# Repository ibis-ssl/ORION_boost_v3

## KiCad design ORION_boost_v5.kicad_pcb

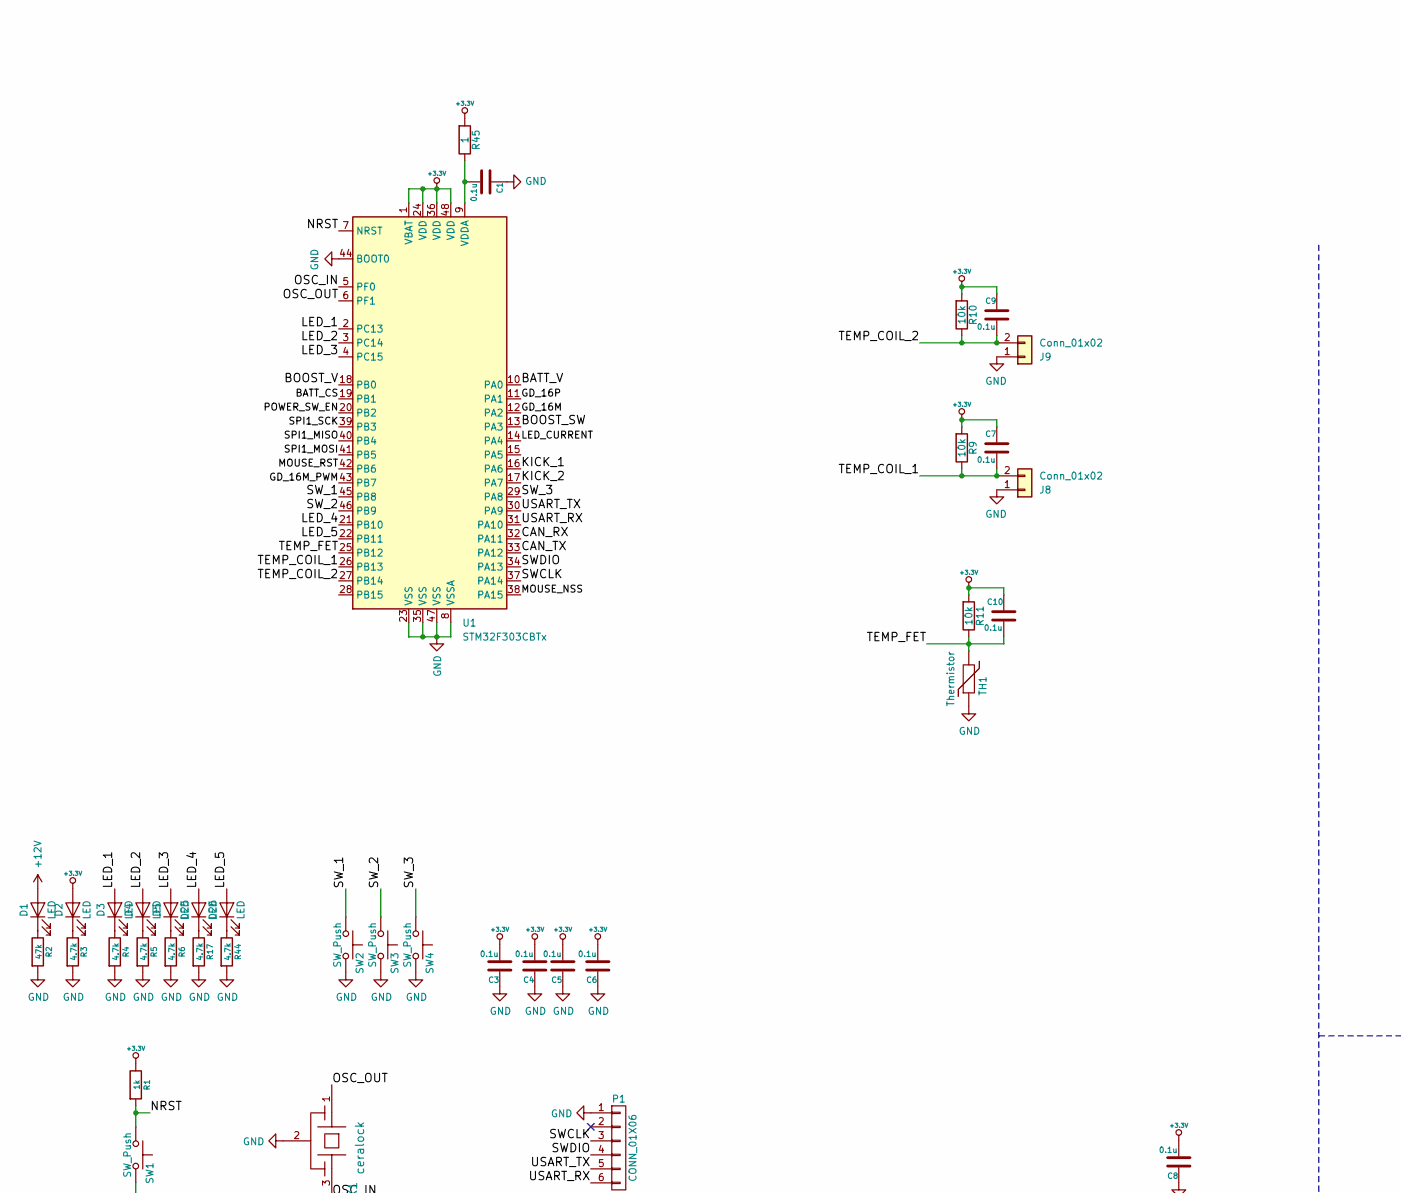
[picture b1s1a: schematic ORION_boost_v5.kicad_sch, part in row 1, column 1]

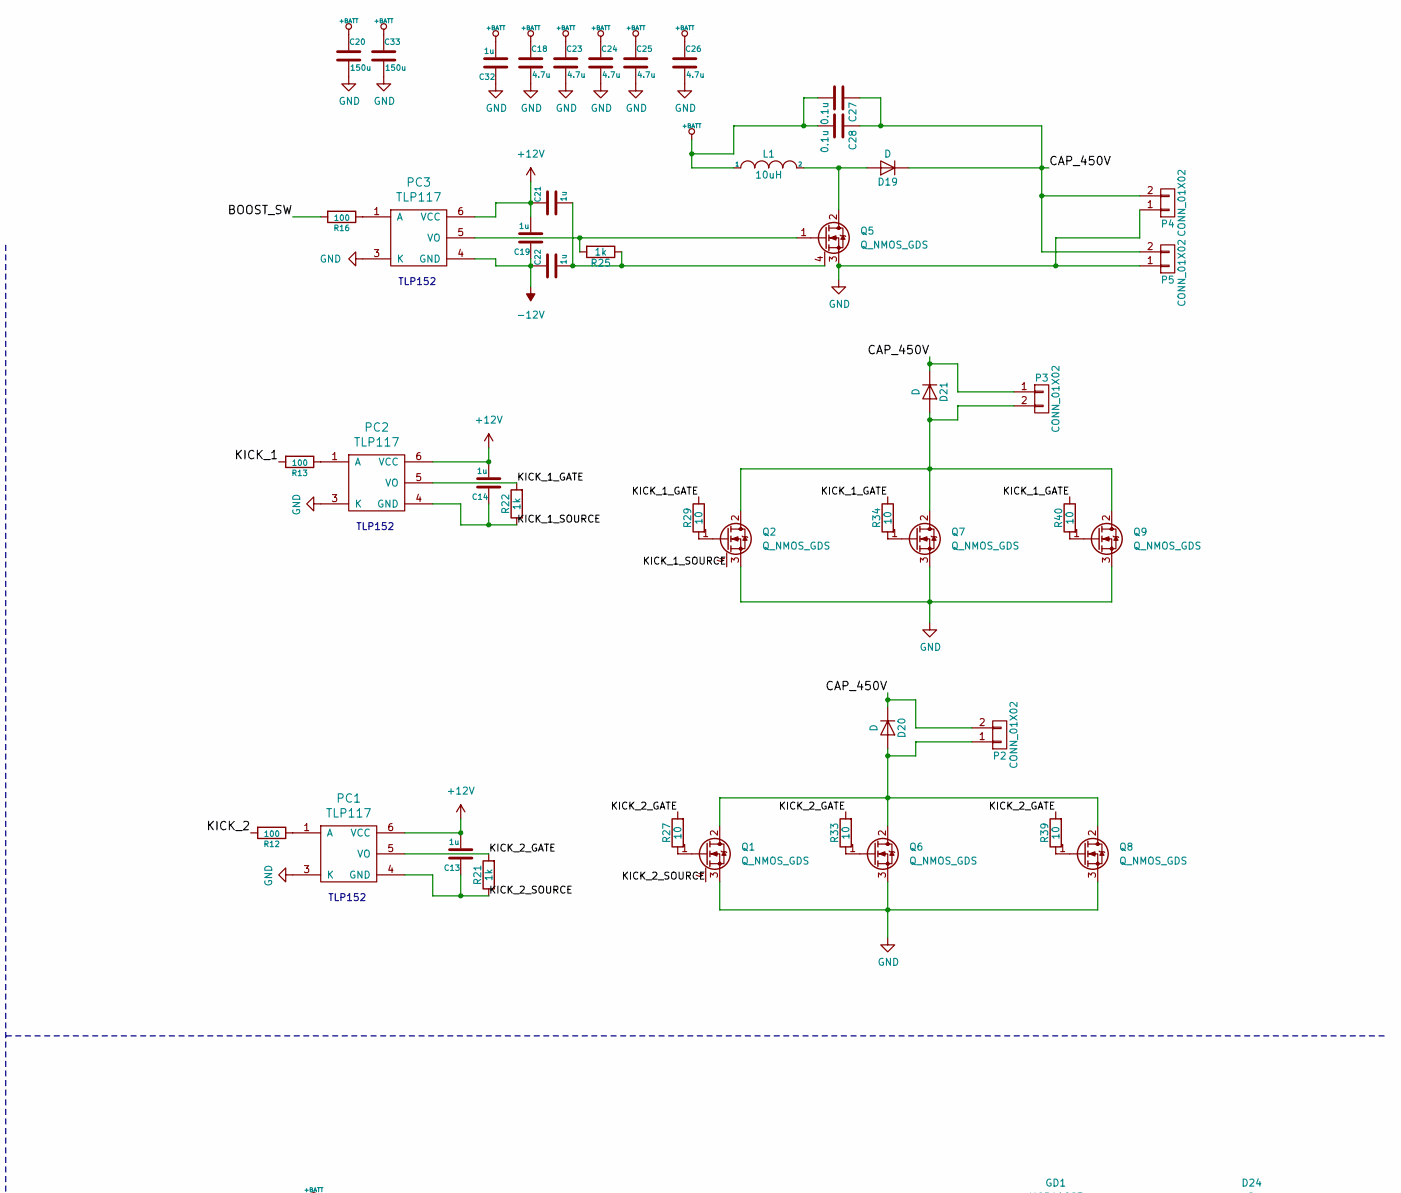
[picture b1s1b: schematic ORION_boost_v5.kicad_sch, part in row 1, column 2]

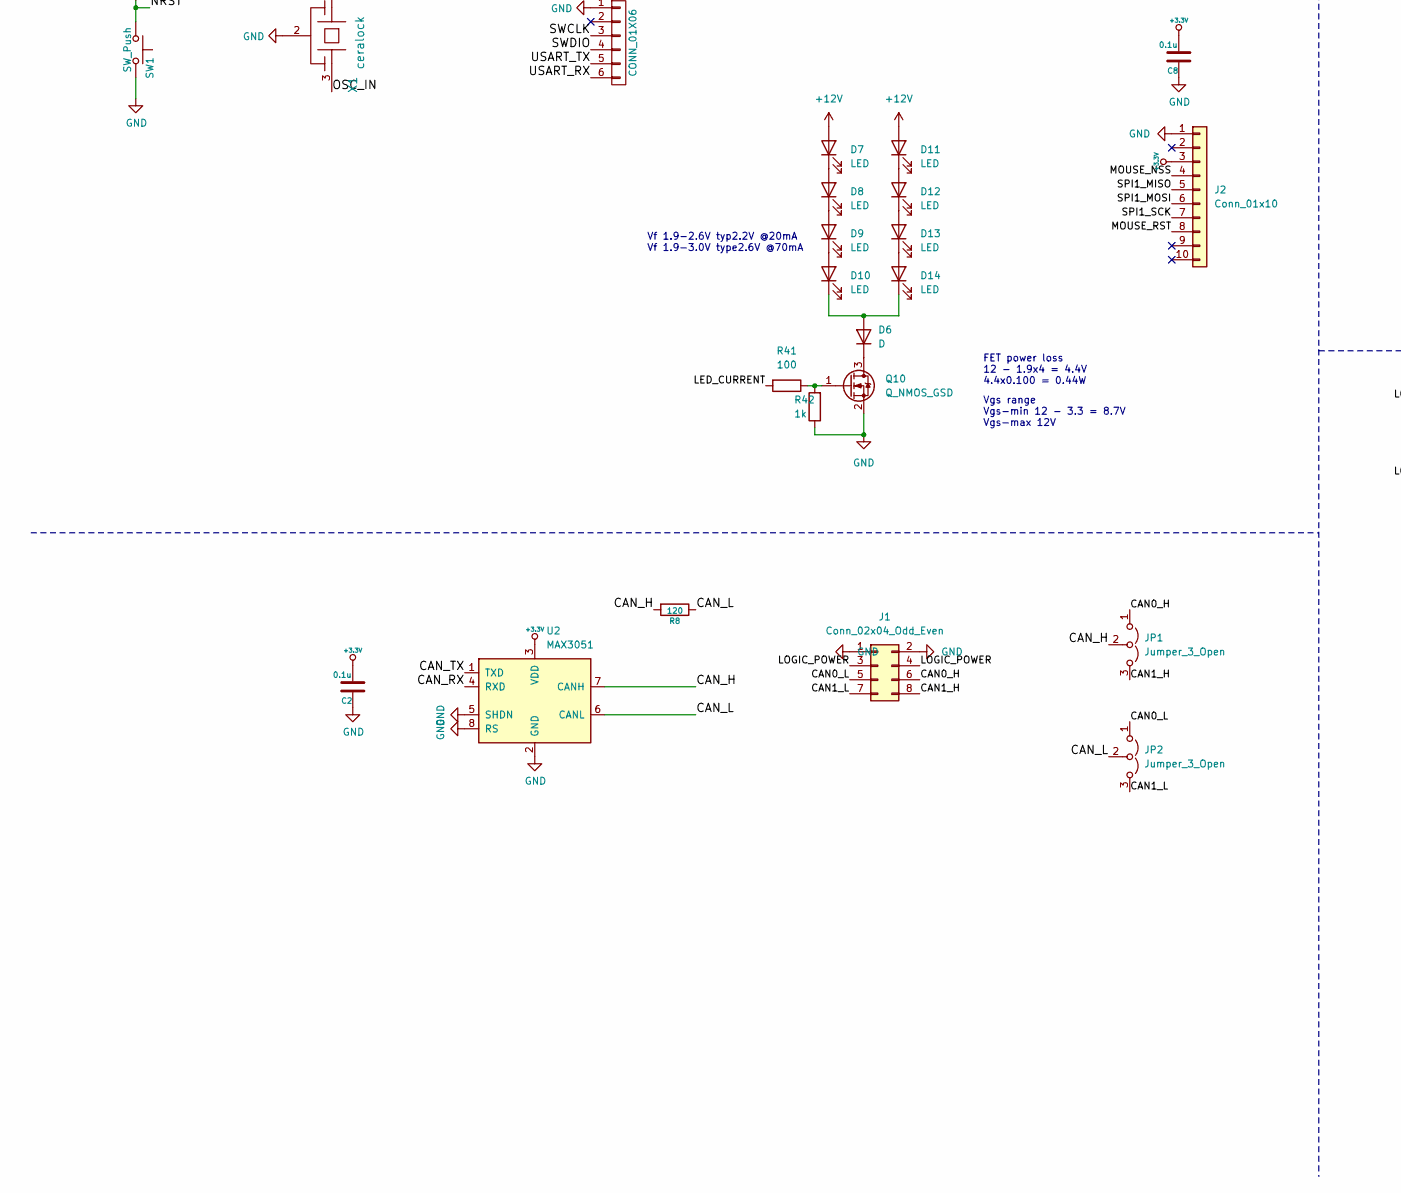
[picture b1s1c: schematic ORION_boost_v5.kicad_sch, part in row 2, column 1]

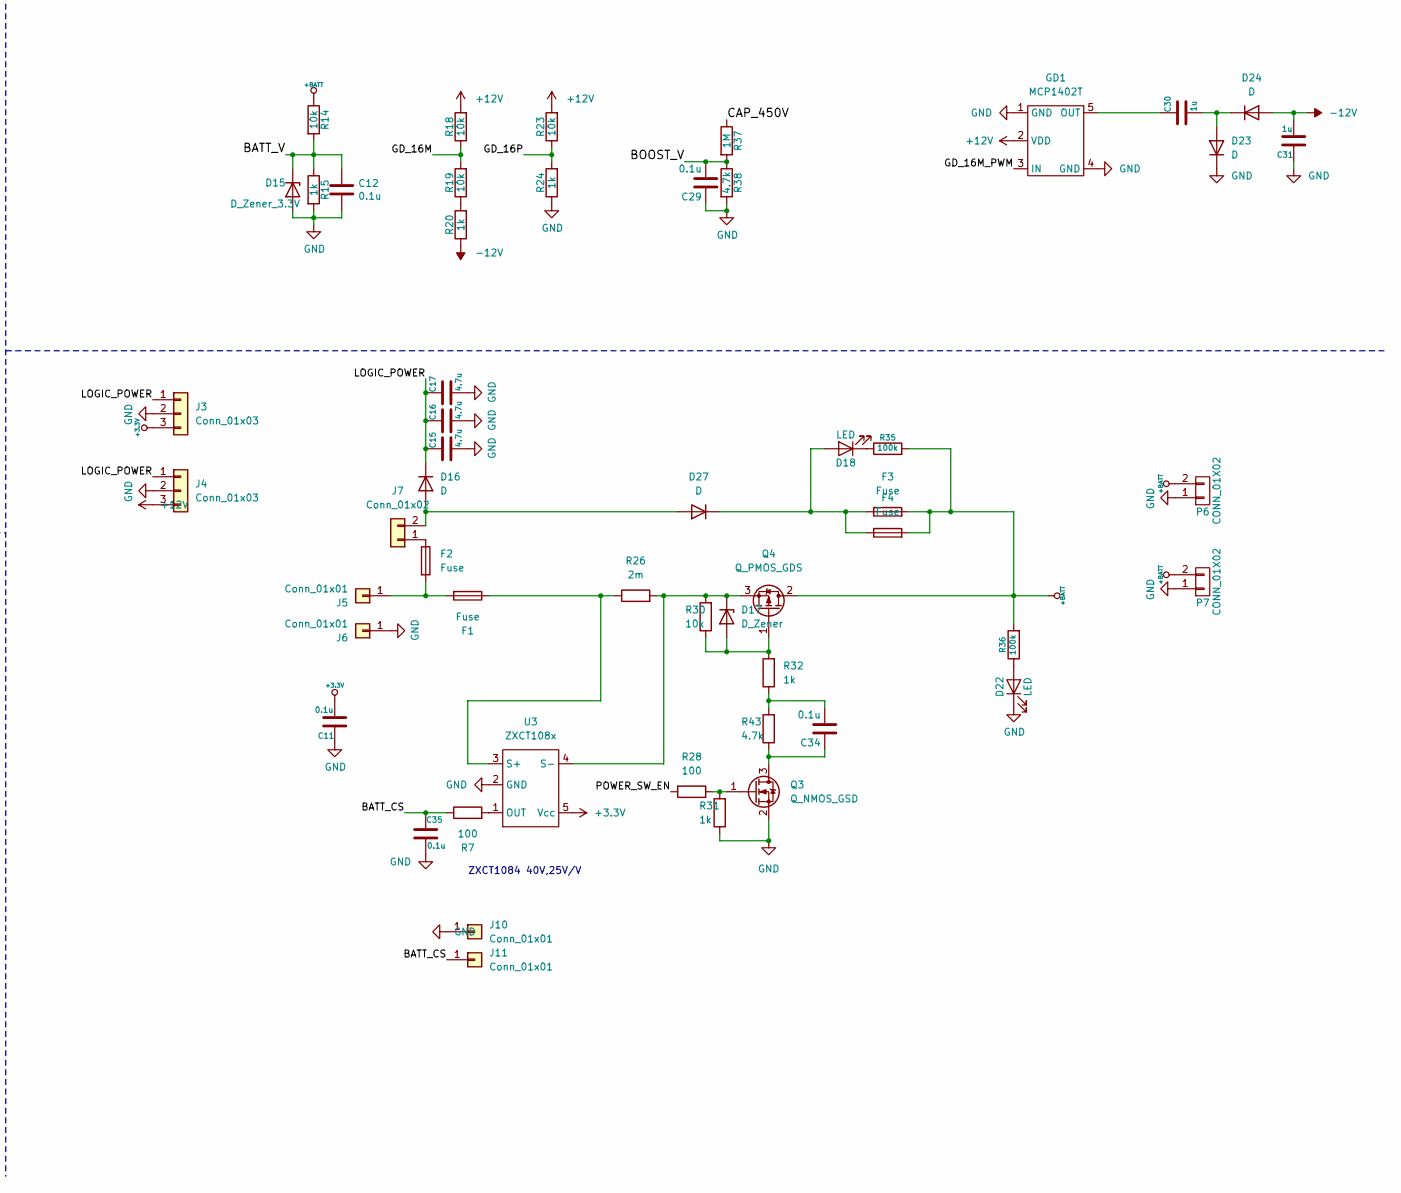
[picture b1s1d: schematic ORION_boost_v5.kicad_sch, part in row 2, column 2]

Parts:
C1, C2, C3, C4, C5, C6, C7, C8, C9, C10, C11, C12, C29, C34, C35: 0.1u; C_0603_1608Metric
C13, C14, C19, C21, C22, C30, C31, C32: 1u; C_0603_1608Metric
C15, C16, C17, C18, C23, C24, C25, C26: 4.7u; C_1206_3216Metric
C20, C33: 150u; CP_Radial_D8.0mm_P3.50mm
C27, C28: 0.1u; C_Rect_L16.5mm_W5.0mm_P15.00mm_MKT
D1, D2, D3, D4, D5, D18, D22, D25, D26: LED; LED_0603_1608Metric
D6: D; D_PowerDI-123
D7, D8, D9, D10, D11, D12, D13, D14: LED; LED_D3.0mm
D15: D_Zener_3.3V; D_SOD-323_HandSoldering
D16, D27: D; D_SMA
D17: D_Zener; D_SOD-323_HandSoldering
D19, D20, D21: D; TO-252-2-RD
D23, D24: D; D_SOD-323_HandSoldering
F1: Fuse; Reusable_Breaker_Top
F2: Fuse; C_Disc_D8.0mm_W2.5mm_P5.00mm
F3, F4: Fuse; Fuse_1210_3225Metric
GD1: MCP1402T; SOT-23-5
J1: Conn_02x04_Odd_Even; Hirose_DF11-8DP-2DSA_2x04_P2.00mm_Vertical
J2: Conn_01x10; PinSocket_1x10_P2.54mm_Vertical
J3, J4: Conn_01x03; VX07805-500
J5, J6: Conn_01x01; TestPoint_Plated_Hole_D3.0mm
J7: Conn_01x02; JST_PH_B2B-PH-K_1x02_P2.00mm_Vertical
J8, J9: Conn_01x02; PinHeader_2x01_P2.00mm_Vertical_SMD
J10, J11: Conn_01x01; WireSoldingPad
JP1, JP2: Jumper_3_Open; SolderJumper-3_P1.3mm_Open_RoundedPad1.0x1.5mm
L1: 10uH; L_Bourns_SRP1770TA_16.9x16.9mm
P1: CONN_01X06; ZH_B6B-ZR
P2, P3, P4, P5: CONN_01X02; Hirose_DF63M-2P-3.96DSA_1x02_P3.96mm_Vertical_pinless
P6, P7: CONN_01X02; AMASS_XT30U-M_1x02_P5.0mm_Vertical
PC1, PC2, PC3: TLP117; SSO-6_6.8x4.6mm_P1.27mm_Clearance8mm
Q1, Q2: Q_NMOS_GDS; TO-252-2_diff
Q3, Q10: Q_NMOS_GSD; SOT-23
Q4: Q_PMOS_GDS; TO-252-2
Q5: Q_NMOS_GDS; TO-220F-3_Horizontal_TabDown_HV_INV_diff
Q6, Q7, Q8, Q9: Q_NMOS_GDS; TO-252-2
R1, R15, R20, R21, R22, R24, R25, R31, R32, R42: 1k; R_0603_1608Metric
R2: 47k; R_0603_1608Metric
R3, R4, R5, R6, R17, R38, R43, R44: 4.7k; R_0603_1608Metric
R7, R12, R13, R16, R28, R41: 100; R_0603_1608Metric
R8: 120; R_0603_1608Metric
R9, R10, R11, R14, R18, R19, R23, R30: 10k; R_0603_1608Metric
R26: 2m; R_1020_2550Metric
R27, R29, R33, R34, R39, R40: 10; R_0603_1608Metric
R35, R36: 100k; R_0603_1608Metric
R37: 1M; R_1206_3216Metric
R45: 1; R_0603_1608Metric
SW1, SW2, SW3, SW4: SW_Push; SW_Push_SPST_NO_Alps_SKRK
TH1: Thermistor; R_0603_1608Metric
U1: STM32F303CBTx; LQFP-48_7x7mm_P0.5mm
U2: MAX3051; SO-8_3.9x4.9mm_P1.27mm
U3: ZXCT108x; SOT-23-5
X1: ceralock; Resonator_SMD_Murata_CSTxExxV-3Pin_3.0x1.1mm

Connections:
+3.3V: C2.2, C3.2, C4.2, C5.2, C6.2, C7.1, C8.2, C9.1, C10.1, C11.2, D2.2 (A), J2.3, J3.3, R1.1, R9.2, R10.2, R11.2, R45.2, U1.1 (VBAT), U1.24 (VDD), U1.36 (VDD), U1.48 (VDD), U2.3 (VDD), U3.5 (Vcc)
+12V: C13.2, C14.2, C19.2, C21.1, D1.2 (A), D7.2 (A), D11.2 (A), GD1.2 (VDD), J4.3, PC1.6 (VCC), PC2.6 (VCC), PC3.6 (VCC), R18.2, R23.2
+BATT: C18.1, C20.1, C23.1, C24.1, C25.1, C26.1, C27.2, C28.2, C32.2, C33.1, F3.2, F4.2, L1.1, P6.2, P7.2, Q4.2 (D), R14.1, R35.2, R36.2
-12V: C19.1, C22.1, C31.2, D24.2 (A), PC3.4 (GND), R20.1
/BATT_CS: C35.1, J11.1, R7.1, U1.19 (PB1)
/BATT_V: C12.2, D15.1 (K), R14.2, R15.1, U1.10 (PA0)
/BOOST_SW: R16.2, U1.13 (PA3)
/BOOST_V: C29.2, R37.2, R38.1, U1.18 (PB0)
/CAN0_H: J1.6, JP1.1 (A)
/CAN0_L: J1.5, JP2.1 (A)
/CAN1_H: J1.8, JP1.3 (B)
/CAN1_L: J1.7, JP2.3 (B)
/CAN_H: JP1.2 (C), R8.2, U2.7 (CANH)
/CAN_L: JP2.2 (C), R8.1, U2.6 (CANL)
/CAN_RX: U1.32 (PA11), U2.4 (RXD)
/CAN_TX: U1.33 (PA12), U2.1 (TXD)
/CAP_450V: C27.1, C28.1, D19.1 (K), D20.1 (K), D21.1 (K), P2.2, P3.1, P4.2, P5.2, R37.1
/GD_16M: R18.1, R19.2, U1.12 (PA2)
/GD_16M_PWM: GD1.3 (IN), U1.43 (PB7)
/GD_16P: R23.1, R24.2, U1.11 (PA1)
/KICK_1: R13.2, U1.16 (PA6)
/KICK_1_GATE: PC2.5 (VO), R22.2, R29.1, R34.1, R40.1
/KICK_1_SOURCE: C14.1, PC2.4 (GND), Q2.4 (S_G), R22.1
/KICK_2: R12.2, U1.17 (PA7)
/KICK_2_GATE: PC1.5 (VO), R21.2, R27.2, R33.2, R39.2
/KICK_2_SOURCE: C13.1, PC1.4 (GND), Q1.4 (S_G), R21.1
/LED_1: D3.2 (A), U1.2 (PC13)
/LED_2: D4.2 (A), U1.3 (PC14)
/LED_3: D5.2 (A), U1.4 (PC15)
/LED_4: D25.2 (A), U1.21 (PB10)
/LED_5: D26.2 (A), U1.22 (PB11)
/LED_CURRENT: R41.2, U1.14 (PA4)
/LOGIC_POWER: C15.1, C16.1, C17.1, D16.1 (K), J1.3, J1.4, J3.1, J4.1; also elsewhere on the board
/MOUSE_NSS: J2.4, U1.38 (PA15)
/MOUSE_RST: J2.8, U1.42 (PB6)
/NRST: R1.2, SW1.1, U1.7 (NRST)
/OSC_IN: U1.5 (PF0), X1.3
/OSC_OUT: U1.6 (PF1), X1.1
/POWER_SW_EN: R28.2, U1.20 (PB2)
/SPI1_MISO: J2.5, U1.40 (PB4)
/SPI1_MOSI: J2.6, U1.41 (PB5)
/SPI1_SCK: J2.7, U1.39 (PB3)
/SWCLK: P1.3, U1.37 (PA14)
/SWDIO: P1.4, U1.34 (PA13)
/SW_1: SW2.1, U1.45 (PB8)
/SW_2: SW3.1, U1.46 (PB9)
/SW_3: SW4.1, U1.29 (PA8)
/TEMP_COIL_1: C7.2, J8.2, R9.1, U1.26 (PB13)
/TEMP_COIL_2: C9.2, J9.2, R10.1, U1.27 (PB14)
/TEMP_FET: C10.2, R11.1, TH1.2, U1.25 (PB12)
/USART_RX: P1.6, U1.31 (PA10)
/USART_TX: P1.5, U1.30 (PA9)
GND: C1.1, C2.1, C3.1, C4.1, C5.1, C6.1, C8.1, C11.1, C12.1, C15.2, C16.2, C17.2, C18.2, C20.2, C23.2, C24.2, C25.2, C26.2, C29.1, C31.1, C32.1, C33.2, C35.2, D15.2 (A), D22.1 (K), D23.1 (K), GD1.1 (GND), GD1.4 (GND), J1.1, J1.2, J2.1, J3.2, J4.2, J6.1, J8.1, J9.1, J10.1, P1.1, P4.1, P5.1, P6.1, P7.1, PC1.3 (K), PC2.3 (K), PC3.3 (K), Q1.3 (S), Q2.3 (S), Q3.2 (S), Q5.3 (S), Q6.3 (S), Q7.3 (S), Q8.3 (S), Q9.3 (S), Q10.2 (S), R2.2, R3.2, R4.2, R5.2, R6.2, R15.2, R17.2, R24.1, R31.1, R38.2, R42.1, R44.2, SW1.2, SW2.2, SW3.2, SW4.2, TH1.1, U1.8 (VSSA), U1.23 (VSS), U1.35 (VSS), U1.44 (BOOT0), U1.47 (VSS), U2.2 (GND), U2.5 (SHDN), U2.8 (RS), U3.2 (GND), X1.2; also elsewhere on the board
unnamed: C34.2, R32.1, R43.2
unnamed: D1.1 (K), R2.1
unnamed: D2.1 (K), R3.1
unnamed: D3.1 (K), R4.1
unnamed: D4.1 (K), R5.1
unnamed: D5.1 (K), R6.1
unnamed: D6.1 (K), Q10.3 (D)
unnamed: D7.1 (K), D8.2 (A)
unnamed: D8.1 (K), D9.2 (A)
unnamed: D9.1 (K), D10.2 (A)
unnamed: D6.2 (A), D10.1 (K), D14.1 (K)
unnamed: D11.1 (K), D12.2 (A)
unnamed: D12.1 (K), D13.2 (A)
unnamed: D13.1 (K), D14.2 (A)
unnamed: D16.2 (A), D27.2 (A), J7.2
unnamed: D17.2 (A), Q4.1 (G), R30.1, R32.2
unnamed: D17.1 (K), Q4.3 (S), R26.2, R30.2, U3.4 (S-)
unnamed: D18.2 (A), D27.1 (K), F3.1, F4.1
unnamed: D18.1 (K), R35.1
unnamed: D19.2 (A), L1.2, Q5.2 (D)
unnamed: D20.2 (A), P2.1, Q1.2 (D), Q6.2 (D), Q8.2 (D)
unnamed: D21.2 (A), P3.2, Q2.2 (D), Q7.2 (D), Q9.2 (D)
unnamed: D22.2 (A), R36.1
unnamed: C30.2, D23.2 (A), D24.1 (K)
unnamed: D25.1 (K), R17.1
unnamed: D26.1 (K), R44.1
unnamed: C30.1, GD1.5 (OUT)
unnamed: F1.2, F2.2, J5.1
unnamed: F2.1, J7.1
unnamed: PC1.1 (A), R12.1
unnamed: PC2.1 (A), R13.1
unnamed: PC3.1 (A), R16.1
unnamed: PC3.5 (VO), Q5.1 (G), R25.2
unnamed: Q1.1 (G), R27.1
unnamed: Q2.1 (G), R29.2
unnamed: C34.1, Q3.3 (D), R43.1
unnamed: Q3.1 (G), R28.1, R31.2
unnamed: C21.2, C22.2, Q5.4 (S_G), R25.1
unnamed: Q6.1 (G), R33.1
unnamed: Q7.1 (G), R34.2
unnamed: Q8.1 (G), R39.1
unnamed: Q9.1 (G), R40.2
unnamed: Q10.1 (G), R41.1, R42.2
unnamed: R19.1, R20.2
unnamed: C1.2, R45.1, U1.9 (VDDA)
unnamed: R7.2, U3.1 (OUT)
unnamed: F1.1, R26.1, U3.3 (S+)

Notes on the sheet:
TLP152
FET power loss 12 - 1.9x4 = 4.4V 4.4x0.100 = 0.44W
ZXCT1084 40V,25V/V
Vgs range Vgs-min 12 - 3.3 = 8.7V Vgs-max 12V
Vf 1.9-2.6V typ2.2V @20mA Vf 1.9-3.0V type2.6V @70mA

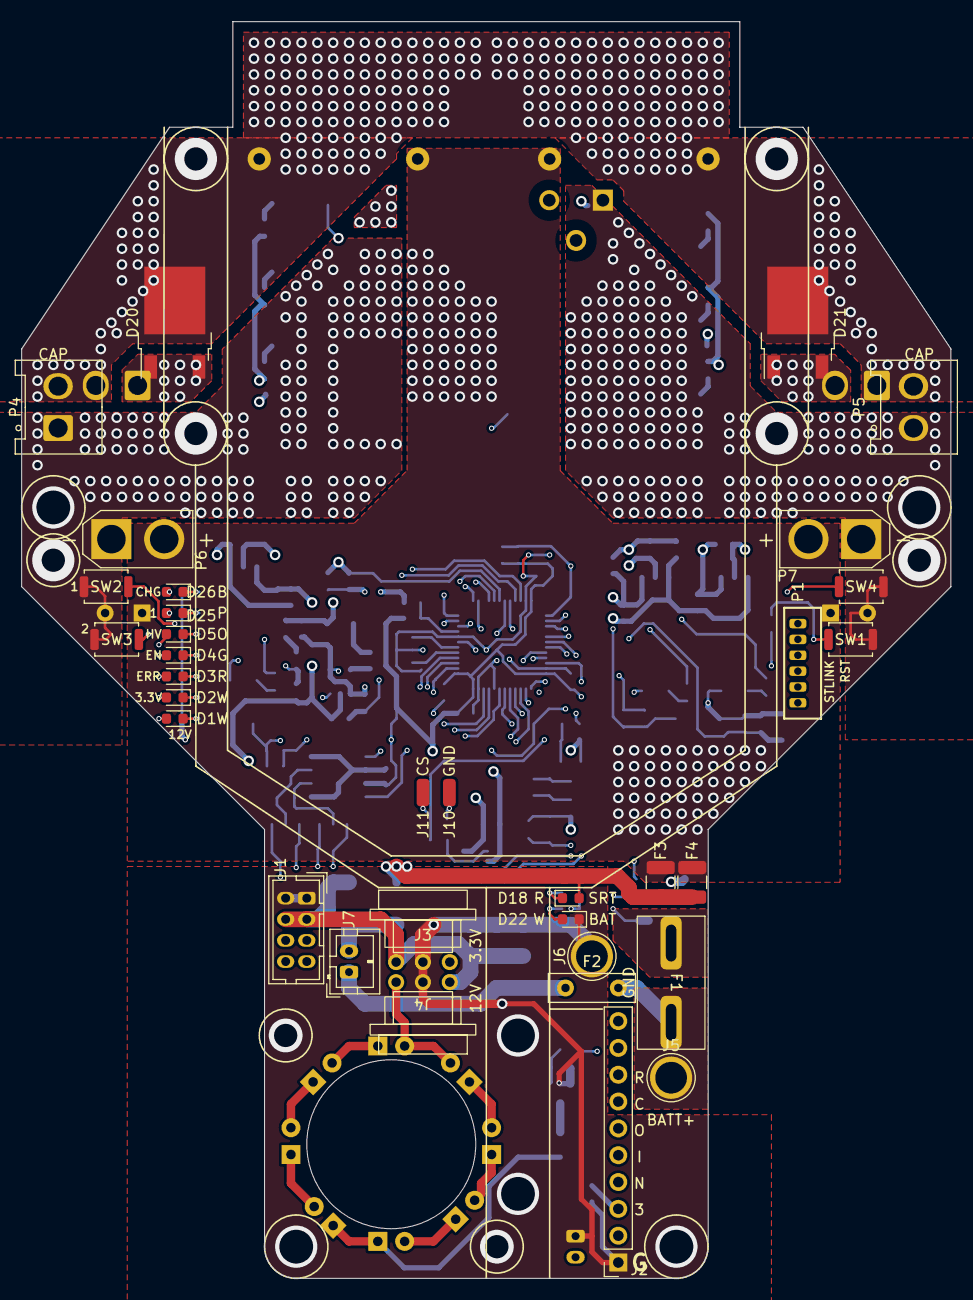
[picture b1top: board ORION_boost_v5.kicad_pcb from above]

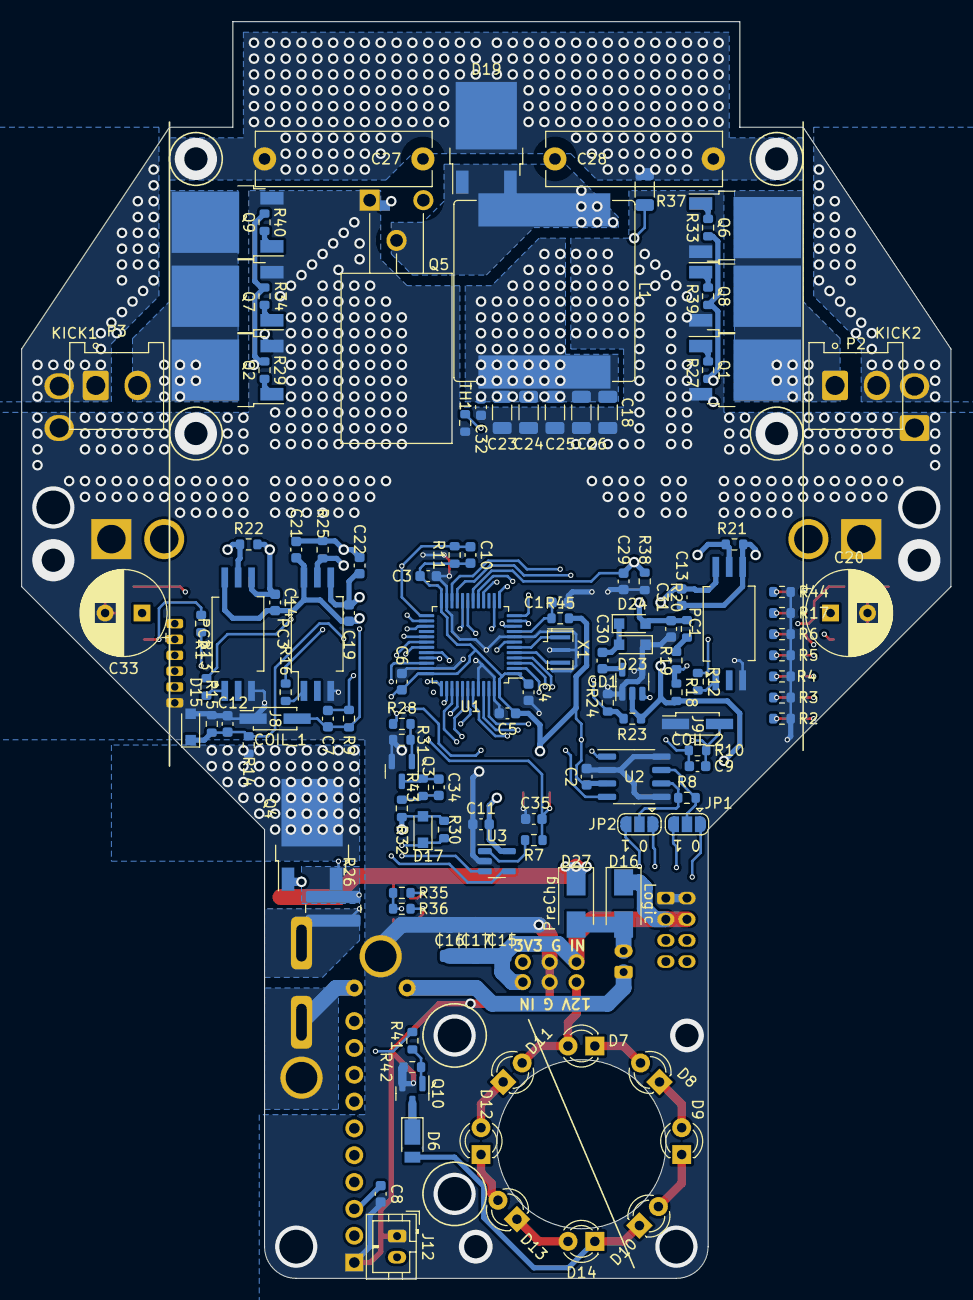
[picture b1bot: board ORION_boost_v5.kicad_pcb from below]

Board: 4 copper layers, 88.0 x 119.0 mm, 156 parts (123 on the bottom side), 100 nets.

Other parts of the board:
J12: Conn_01x02; JST_PH_B2B-PH-K_1x02_P2.00mm_Vertical

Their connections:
/LOGIC_POWER: J12.2; also elsewhere on the board
GND: J12.1; also elsewhere on the board

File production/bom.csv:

Designator,Footprint,Quantity,Value,LCSC Part #
"C1, C10, C11, C12, C2, C29, C3, C34, C35, C4, C5, C6, C7, C8, C9",0603,15,0.1u,
"C13, C14, C19, C21, C22, C30, C31, C32",0603,8,1u,
"C15, C16, C17, C18, C23, C24, C25, C26",1206,8,4.7u,
"C20, C33",CP_Radial_D8.0mm_P3.50mm,2,150u,
"C27, C28",C_Rect_L16.5mm_W5.0mm_P15.00mm_MKT,2,0.1u,
"D1, D18, D2, D22, D25, D26, D3, D4, D5",0603,9,LED,
"D10, D11, D12, D13, D14, D7, D8, D9",LED_D3.0mm,8,LED,
D15,D_SOD-323_HandSoldering,1,D_Zener_3.3V,
"D16, D27",D_SMA,2,D,
D17,D_SOD-323_HandSoldering,1,D_Zener,
"D19, D20, D21",TO-252-2-RD,3,D,
"D23, D24",D_SOD-323_HandSoldering,2,D,
D6,D_PowerDI-123,1,D,
F1,Reusable_Breaker_Top,1,Fuse,
F2,C_Disc_D8.0mm_W2.5mm_P5.00mm,1,Fuse,
"F3, F4",1210,2,Fuse,
GD1,SOT-23-5,1,MCP1402T,
J1,Hirose_DF11-8DP-2DSA_2x04_P2.00mm_Vertical,1,Conn_02x04_Odd_Even,
"J10, J11",WireSoldingPad,2,Conn_01x01,
"J12, J7",JST_PH_B2B-PH-K_1x02_P2.00mm_Vertical,2,Conn_01x02,
J2,PinSocket_1x10_P2.54mm_Vertical,1,Conn_01x10,
"J3, J4",VX07805-500,2,Conn_01x03,
"J5, J6",TestPoint_Plated_Hole_D3.0mm,2,Conn_01x01,
"J8, J9",PinHeader_2x01_P2.00mm_Vertical_SMD,2,Conn_01x02,
"JP1, JP2",SolderJumper-3_P1.3mm_Open_RoundedPad1.0x1.5mm,2,Jumper_3_Open,
L1,L_Bourns_SRP1770TA_16.9x16.9mm,1,10uH,
P1,ZH_B6B-ZR,1,CONN_01X06,
"P2, P3, P4, P5",Hirose_DF63M-2P-3.96DSA_1x02_P3.96mm_Vertical_pinless,4,CONN_01X02,
"P6, P7",AMASS_XT30U-M_1x02_P5.0mm_Vertical,2,CONN_01X02,
"PC1, PC2, PC3",SSO-6_6.8x4.6mm_P1.27mm_Clearance8mm,3,TLP117,
"Q1, Q2",TO-252-2_diff,2,Q_NMOS_GDS,
"Q10, Q3",SOT-23,2,Q_NMOS_GSD,
Q4,TO-252-2,1,Q_PMOS_GDS,
Q5,TO-220F-3_Horizontal_TabDown_HV_INV_diff,1,Q_NMOS_GDS,
"Q6, Q7, Q8, Q9",TO-252-2,4,Q_NMOS_GDS,
"R1, R15, R20, R21, R22, R24, R25, R31, R32, R42",0603,10,1k,
"R10, R11, R14, R18, R19, R23, R30, R9",0603,8,10k,
"R12, R13, R16, R28, R41, R7",0603,6,100,
"R17, R3, R38, R4, R43, R44, R5, R6",0603,8,4.7k,
R2,0603,1,47k,
R26,1020,1,2m,
"R27, R29, R33, R34, R39, R40",0603,6,10,
"R35, R36",0603,2,100k,
R37,1206,1,1M,
R45,0603,1,1,
R8,0603,1,120,
"SW1, SW2, SW3, SW4",SW_Push_SPST_NO_Alps_SKRK,4,SW_Push,
TH1,0603,1,Thermistor,
U1,LQFP-48_7x7mm_P0.5mm,1,STM32F303CBTx,
U2,SO-8_3.9x4.9mm_P1.27mm,1,MAX3051,
U3,SOT-23-5,1,ZXCT108x,
X1,Resonator_SMD_Murata_CSTxExxV-3Pin_3.0x1.1mm,1,ceralock,

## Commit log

2022-12-07 天丼マン
2022-12-08 ビアうち、レイアウト調整、GNDライン構築、メカ寸法調整(途中)
2022-12-09 シルク･ビア最終調整、銅線貼り付け猶予
2022-12-10 ベタパターンの調整
2023-04-05 発注done
2023-12-17 電源スイッチの取り扱い変更、幅縮小
2024-11-02 KiCAD8.0に更新
2024-11-17 KiCAD8に更新
2024-11-17 PCBA発注
2025-01-21 v5発注
